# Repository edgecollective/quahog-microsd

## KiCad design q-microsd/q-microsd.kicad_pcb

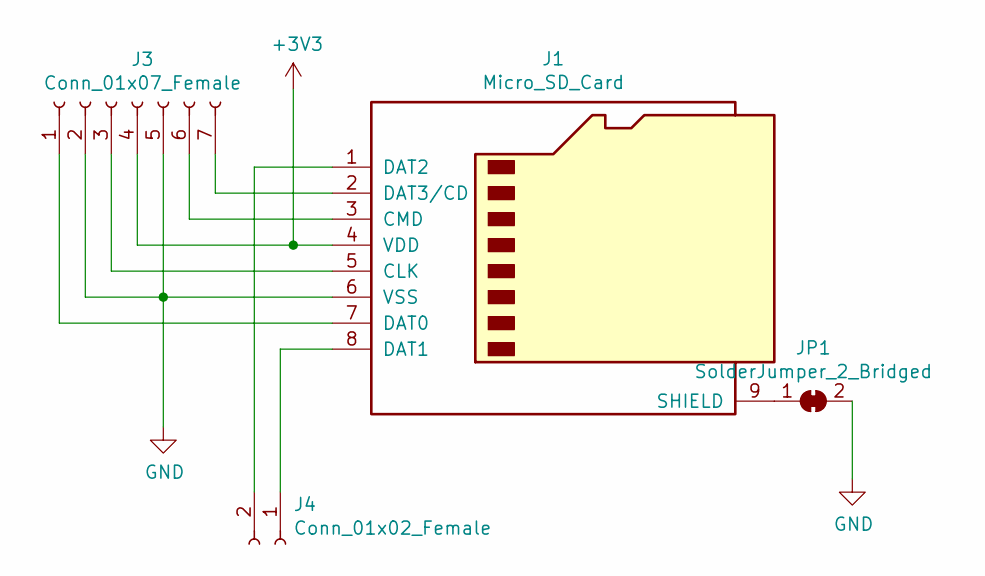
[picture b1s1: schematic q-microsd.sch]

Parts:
J1: Micro_SD_Card; microSD_HC_Hirose_DM3D-SF
J3: Conn_01x07_Female; PinHeader_1x07_P2.54mm_Horizontal
J4: Conn_01x02_Female; PinSocket_1x02_P2.54mm_Vertical
JP1: SolderJumper_2_Bridged; SolderJumper-2_P1.3mm_Bridged_RoundedPad1.0x1.5mm

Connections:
+3V3: J1.4 (VDD), J3.4
GND: J1.6 (VSS), J3.2, J3.5, JP1.2 (B)
unnamed: J1.1 (DAT2), J4.2
unnamed: J1.2 (DAT3/CD), J3.7
unnamed: J1.3 (CMD), J3.6
unnamed: J1.5 (CLK), J3.3
unnamed: J1.7 (DAT0), J3.1
unnamed: J1.8 (DAT1), J4.1
unnamed: J1.9 (SHIELD), JP1.1 (A)

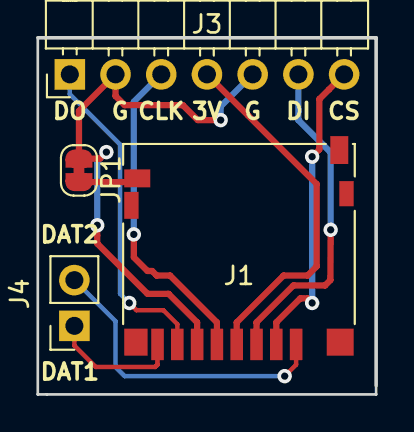
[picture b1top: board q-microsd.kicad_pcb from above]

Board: 2 copper layers, 18.8 x 19.8 mm, 4 parts (0 on the bottom side), 9 nets.
